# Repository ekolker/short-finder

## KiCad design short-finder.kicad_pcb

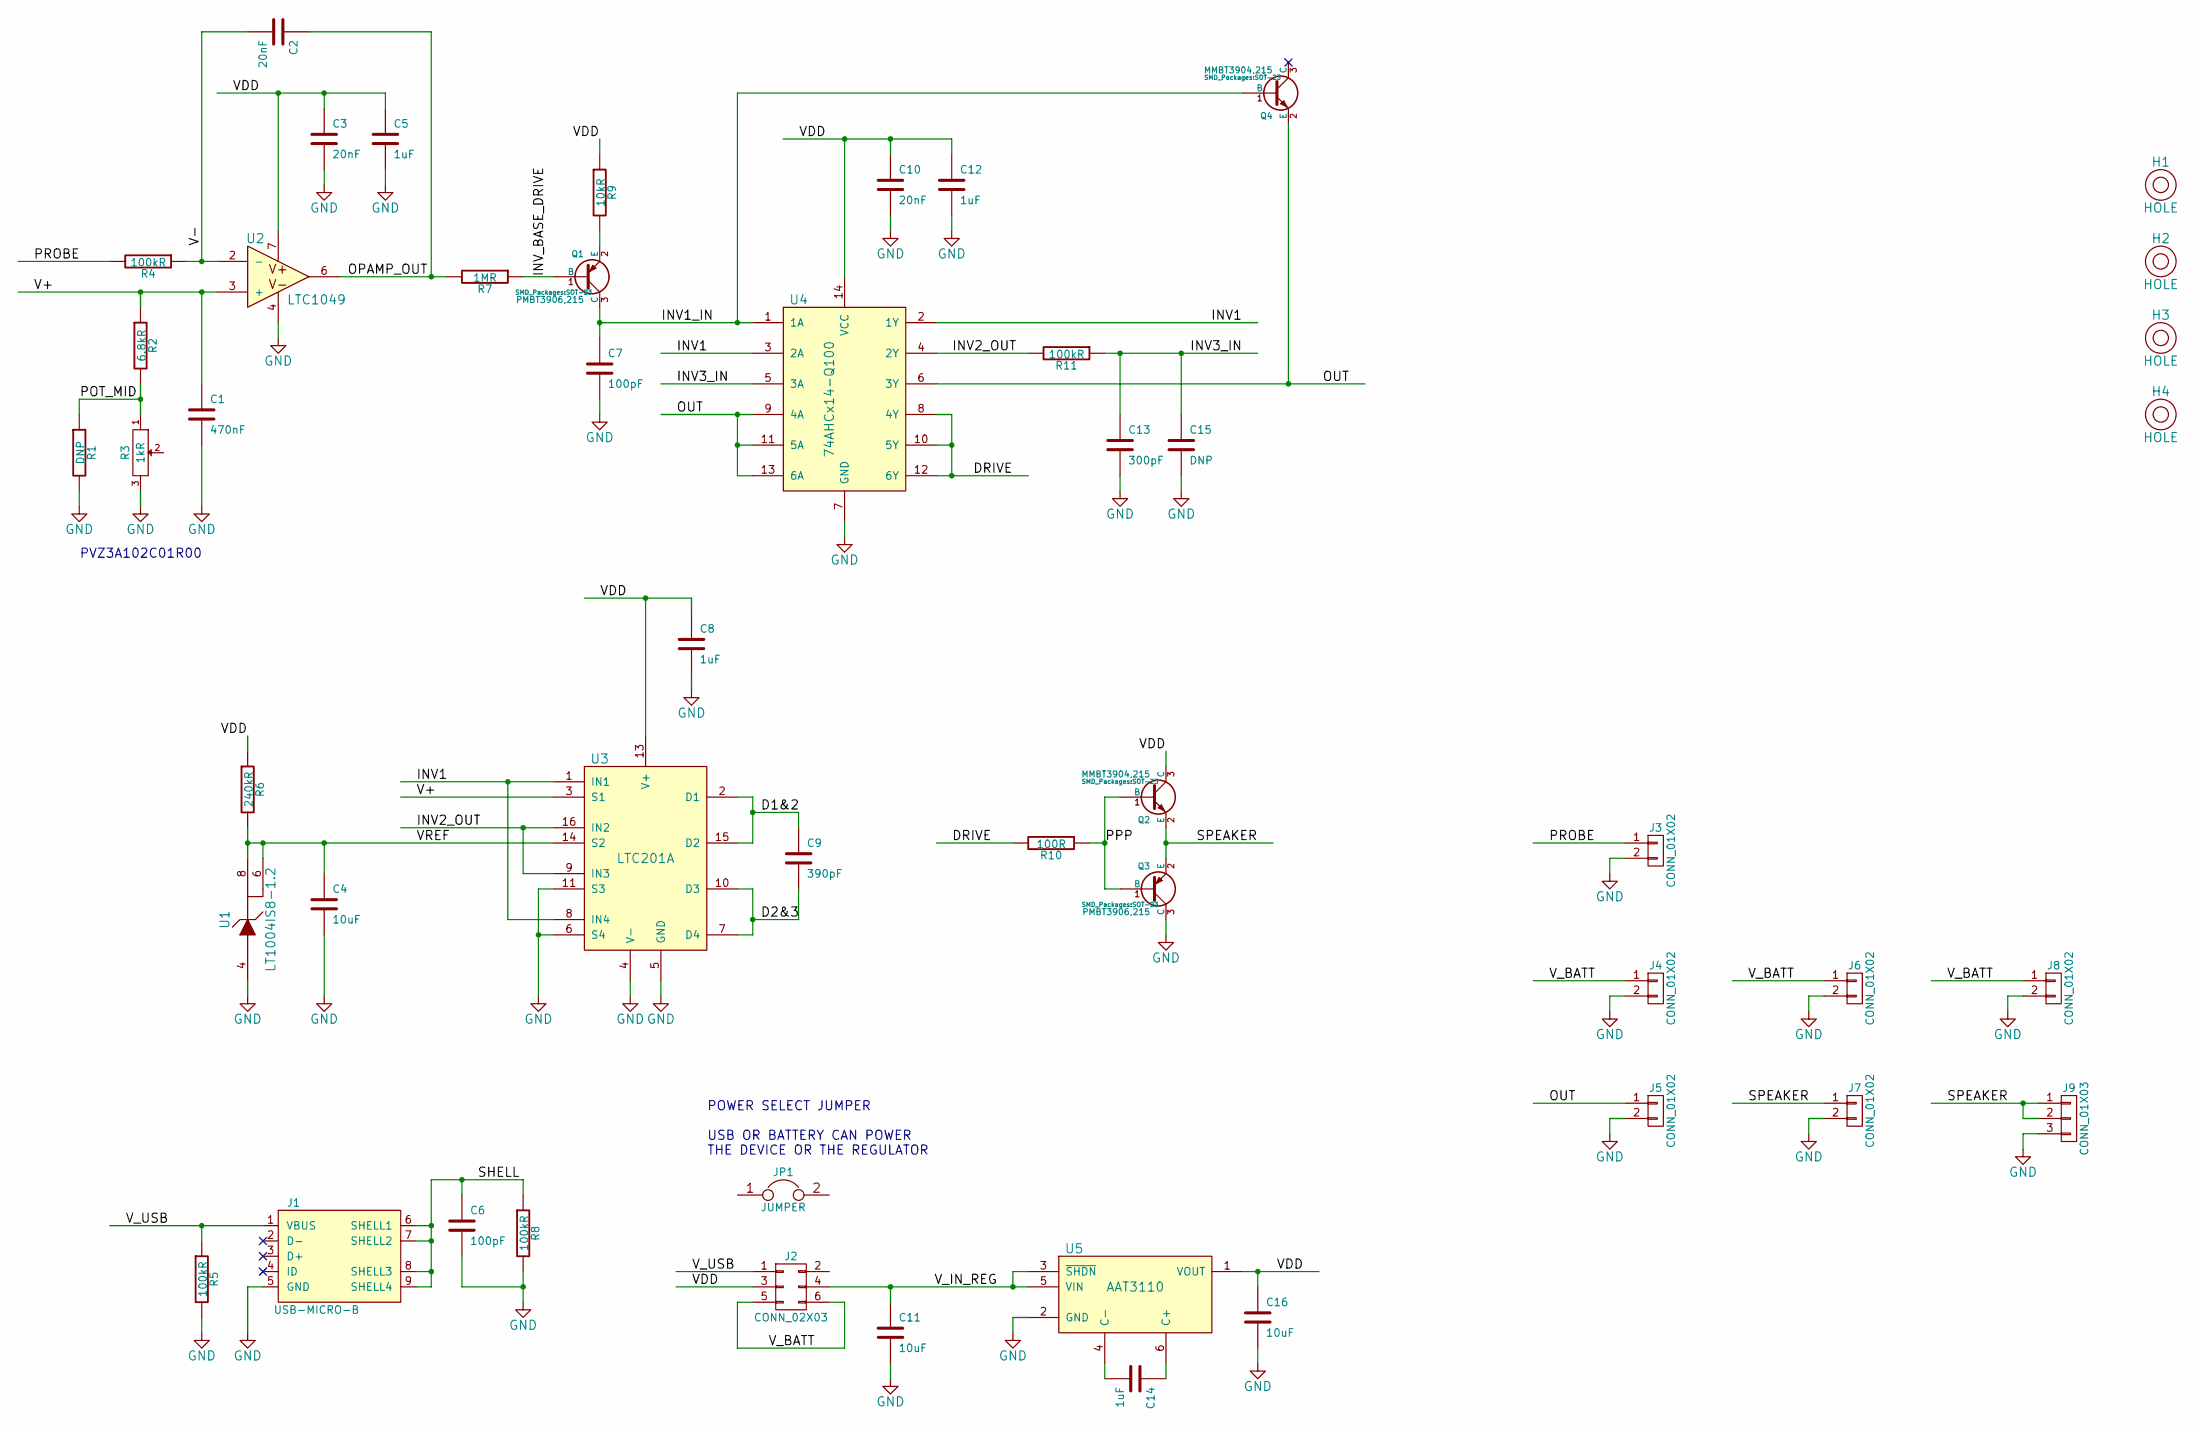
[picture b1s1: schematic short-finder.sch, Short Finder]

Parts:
C1: 470nF; SMD-0402-C
C2, C3, C10: 20nF; SMD-0402-C
C4, C11: 10uF; SMD-0402-C
C5, C8, C12, C14: 1uF; SMD-0402-C
C6, C7: 100pF; SMD-0402-C
C9: 390pF; SMD-0402-C
C13: 300pF; SMD-0402-C
C15: DNP; SMD-0402-C
C16: 10uF; SMD-0805
H1, H2, H3, H4: HOLE; M2-HOLE
J1: USB-MICRO-B; MICRO-USB-10104111
J2: CONN_02X03; Pin_Header_Straight_2x03
J3: CONN_01X02; POMONA_6883
J4, J5, J6, J7, J8: CONN_01X02; Pin_Header_Straight_1x02
J9: CONN_01X03; Pin_Header_Straight_1x03
JP1: JUMPER
Q1, Q3: PMBT3906,215; SOT-23
Q2, Q4: MMBT3904,215; SOT-23
R1: DNP; SMD-0402-R
R2: 6.8kR; SMD-0402-R
R3: 1kR; PVZ3A
R4, R5, R8, R11: 100kR; SMD-0402-R
R6: 240kR; SMD-0402-R
R7: 1MR; SMD-0402-R
R9: 10kR; SMD-0402-R
R10: 100R; SMD-0402-R
U1: LT1004IS8-1.2; SOIC-8_3.9x4.9mm_Pitch1.27mm
U2: LTC1049; SOIC-8_3.9x4.9mm_Pitch1.27mm
U3: LTC201A; SOIC-16_3.9x9.9mm_Pitch1.27mm
U4: 74AHCx14-Q100; SOIC-14_3.9x8.7mm_Pitch1.27mm
U5: AAT3110; SOT-23-6

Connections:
/D1&2: C9.1, U3.2 (D1), U3.15 (D2)
/D2&3: C9.2, U3.7 (D4), U3.10 (D3)
/DRIVE: R10.2, U4.8 (4Y), U4.10 (5Y), U4.12 (6Y)
/INV1: U3.1 (IN1), U3.8 (IN4), U4.2 (1Y), U4.3 (2A)
/INV1_IN: C7.1, Q1.3 (C), Q4.1 (B), U4.1 (1A)
/INV2_OUT: R11.2, U3.9 (IN3), U3.16 (IN2), U4.4 (2Y)
/INV3_IN: C13.1, C15.1, R11.1, U4.5 (3A)
/INV_BASE_DRIVE: Q1.1 (B), R7.1
/OPAMP_OUT: C2.1, R7.2, U2.6
/OUT: J5.1, Q4.2 (E), U4.6 (3Y), U4.9 (4A), U4.11 (5A), U4.13 (6A)
/POT_MID: R1.1, R2.2, R3.1
/PPP: Q2.1 (B), Q3.1 (B), R10.1
/PROBE: J3.1, R4.2
/SHELL: C6.1, J1.6 (SHELL1), J1.7 (SHELL2), J1.8 (SHELL3), J1.9 (SHELL4), R8.1
/SPEAKER: J7.1, J9.1, J9.2, Q2.2 (E), Q3.2 (E)
/V+: C1.1, R2.1, U2.3 (+), U3.3 (S1)
/V-: C2.2, R4.1, U2.2 (-)
/VDD: C3.1, C5.1, C8.1, C10.1, C12.1, C16.1, J2.3, Q2.3 (C), R6.1, R9.1, U2.7, U3.13 (V+), U4.14 (VCC), U5.1 (VOUT)
/VREF: C4.1, R6.2, U1.6, U1.8, U3.14 (S2)
/V_BATT: J2.5, J2.6, J4.1, J6.1, J8.1
/V_IN_REG: C11.1, J2.4, U5.3 (~SHDN), U5.5 (VIN)
/V_USB: J1.1 (VBUS), J2.1, R5.1
GND: C1.2, C3.2, C4.2, C5.2, C6.2, C7.2, C8.2, C10.2, C11.2, C12.2, C13.2, C15.2, C16.2, J1.5 (GND), J3.2, J4.2, J5.2, J6.2, J7.2, J8.2, J9.3, Q3.3 (C), R1.2, R3.3, R5.2, R8.2, U1.4, U2.4, U3.4 (V-), U3.5 (GND), U3.6 (S4), U3.11 (S3), U4.7 (GND), U5.2 (GND)
unnamed: C14.1, U5.6 (C+)
unnamed: C14.2, U5.4 (C-)
unnamed: Q1.2 (E), R9.2
unnamed: U1.1 (NC), U1.2 (NC), U1.3 (NC), U1.5 (NC), U1.7 (NC)

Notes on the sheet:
POWER SELECT JUMPER USB OR BATTERY CAN POWER THE DEVICE OR THE REGULATOR
PVZ3A102C01R00

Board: 2 copper layers, 49 parts (0 on the bottom side), 27 nets, no tracks yet.

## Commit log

2015-02-07 app note, power system, and output stage in. time to assign values...
2015-02-07 added values, pop options for tweaking
2015-02-11 found a pot, value tweaks
2015-02-11 annotated
2015-02-11 added cache lib
2015-02-11 netlist
2015-02-11 component file
2015-02-11 named (all?) remaining nets
2015-02-11 hello, pcb!
2015-02-11 reannotated slightly and started to think about placement
